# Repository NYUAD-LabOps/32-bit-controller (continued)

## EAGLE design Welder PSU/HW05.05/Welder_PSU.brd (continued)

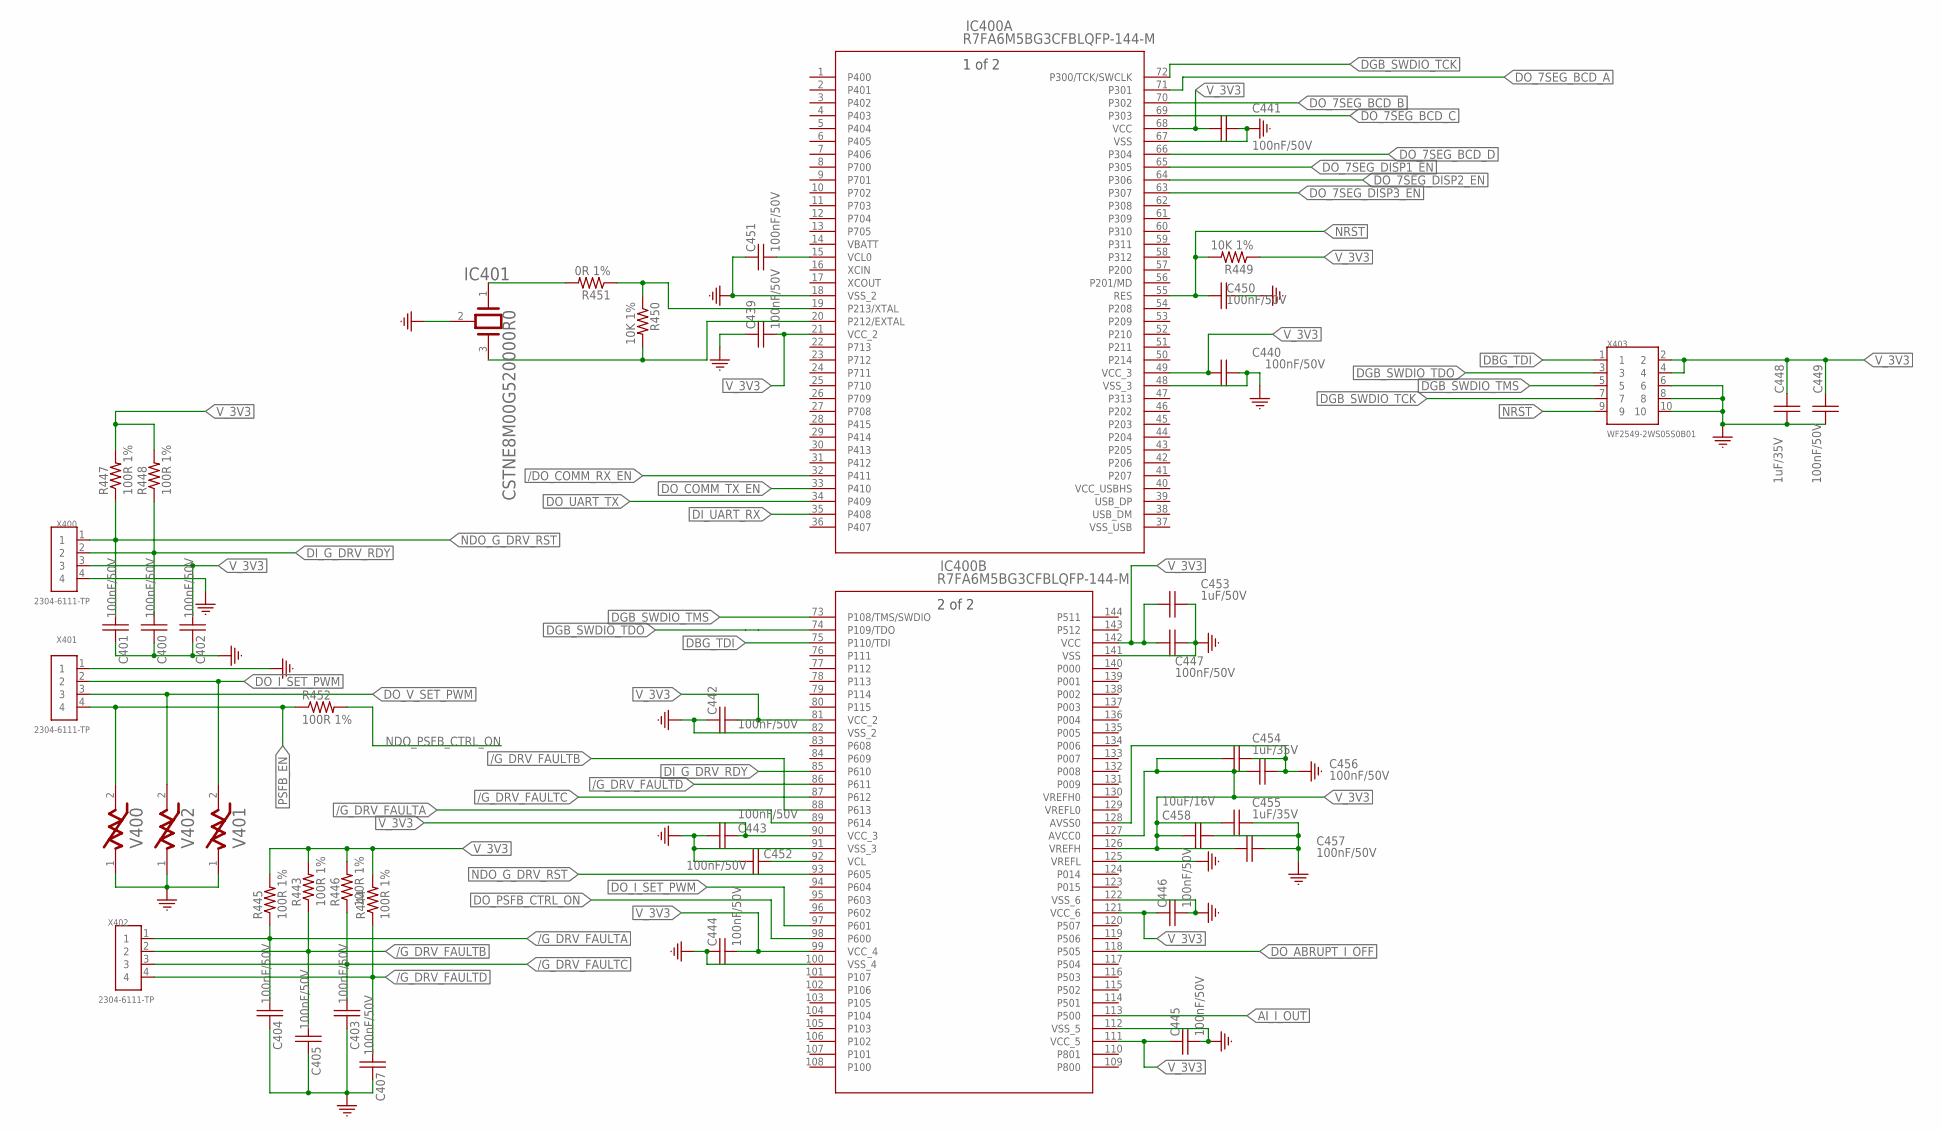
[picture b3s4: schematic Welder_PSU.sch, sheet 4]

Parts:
C400, C401, C402, C403, C404, C405, C407, C439, C440, C441, C442, C443, C444, C445, C446, C447, C449, C450, C451, C452, C456, C457: 100nF/50V; EIA0603
C448, C454, C455: 1uF/35V; EIA0603
C453: 1uF/50V; EIA0603
C458: 10uF/16V; EIA0603
IC400: R7FA6M5BG3CFBLQFP-144-M; LQFP-144-M
IC401: CSTNE8M00G520000R0
R443, R444, R445, R446, R447, R448, R452: 100R 1%; EIA0603
R449, R450: 10K 1%; EIA0603
R451: 0R 1%; EIA0603
V400, V401, V402: 0603ESDA-24NSMD; EIA0603
X400, X401, X402: 2304-6111-TP; X04_100MIL
X403: WF2549-2WS05S0B01; X10_100MIL_2XROW_VERT

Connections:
/DO_COMM_RX_EN: IC400.32 (P411); also elsewhere on the board
/G_DRV_FAULTA: C404.2, IC400.89 (P614), R445.1, X402.1; also elsewhere on the board
/G_DRV_FAULTB: C405.2, IC400.88 (P613), R443.1, X402.2; also elsewhere on the board
/G_DRV_FAULTC: C403.2, IC400.87 (P612), R446.1, X402.3; also elsewhere on the board
/G_DRV_FAULTD: C407.2, IC400.86 (P611), R444.1, X402.4; also elsewhere on the board
AI_I_OUT: IC400.113 (P500); also elsewhere on the board
DBG_TDI: IC400.75 (P110/TDI), X403.1
DGB_SWDIO_TCK: IC400.72 (P300/TCK/SWCLK), X403.7
DGB_SWDIO_TDO: IC400.74 (P109/TDO), X403.3
DGB_SWDIO_TMS: IC400.73 (P108/TMS/SWDIO), X403.5
DI_G_DRV_RDY: C400.2, IC400.85 (P610), R448.1, X400.2; also elsewhere on the board
DI_UART_RX: IC400.35 (P408); also elsewhere on the board
DO_7SEG_BCD_A: IC400.71 (P301); also elsewhere on the board
DO_7SEG_BCD_B: IC400.70 (P302); also elsewhere on the board
DO_7SEG_BCD_C: IC400.69 (P303); also elsewhere on the board
DO_7SEG_BCD_D: IC400.66 (P304); also elsewhere on the board
DO_7SEG_DISP1_EN: IC400.65 (P305); also elsewhere on the board
DO_7SEG_DISP2_EN: IC400.64 (P306); also elsewhere on the board
DO_7SEG_DISP3_EN: IC400.63 (P307); also elsewhere on the board
DO_ABRUPT_I_OFF: IC400.118 (P505); also elsewhere on the board
DO_COMM_TX_EN: IC400.33 (P410); also elsewhere on the board
DO_I_SET_PWM: IC400.97 (P601), V401.2, X401.2; also elsewhere on the board
DO_PSFB_CTRL_ON: IC400.98 (P600)
DO_UART_TX: IC400.34 (P409); also elsewhere on the board
DO_V_SET_PWM: V402.2, X401.3; also elsewhere on the board
GND: C400.1, C401.1, C402.1, C403.1, C404.1, C405.1, C407.1, C439.1, C440.2, C441.2, C442.1, C443.1, C444.1, C445.2, C446.2, C447.2, C448.1, C449.1, C450.2, C451.1, C452.2, C453.2, C454.2, C455.2, C456.2, C457.2, C458.2, IC400.18 (VSS_2), IC400.48 (VSS_3), IC400.67 (VSS), IC400.82 (VSS_2), IC400.91 (VSS_3), IC400.100 (VSS_4), IC400.112 (VSS_5), IC400.122 (VSS_6), IC400.125 (VREFL), IC400.128 (AVSS0), IC400.141 (VSS), IC401.2 (GND), V400.1, V401.1, V402.1, X400.4, X401.1, X403.6, X403.8, X403.10; also elsewhere on the board
unnamed: C451.2, IC400.15 (VCL0)
unnamed: C452.1, IC400.92 (VCL)
unnamed: IC400.20 (P212/EXTAL), IC401.3 (OUTPUT), R450.2
unnamed: IC401.1 (INPUT), R451.2
unnamed: IC400.19 (P213/XTAL), R450.1, R451.1
NDO_G_DRV_RST: C401.2, IC400.93 (P605), R447.1, X400.1; also elsewhere on the board
NDO_PSFB_CTRL_ON: R452.2
NRST: C450.1, IC400.55 (RES), R449.2, X403.9
PSFB_EN: R452.1, V400.2, X401.4; also elsewhere on the board
VBATT: IC400.14 (VBATT)
VCC_USBHS: IC400.40 (VCC_USBHS)
VREFH0: IC400.130 (VREFH0)
VREFL0: IC400.129 (VREFL0)
VSS_USB: IC400.37 (VSS_USB)
V_3V3: C402.2, C439.2, C440.1, C441.1, C442.2, C443.2, C444.2, C445.1, C446.1, C447.1, C448.2, C449.2, C453.1, C454.1, C455.1, C456.1, C457.1, C458.1, IC400.21 (VCC_2), IC400.49 (VCC_3), IC400.68 (VCC), IC400.81 (VCC_2), IC400.90 (VCC_3), IC400.99 (VCC_4), IC400.111 (VCC_5), IC400.121 (VCC_6), IC400.126 (VREFH), IC400.127 (AVCC0), IC400.142 (VCC), R443.2, R444.2, R445.2, R446.2, R447.2, R448.2, R449.1, X400.3, X403.2, X403.4; also elsewhere on the board

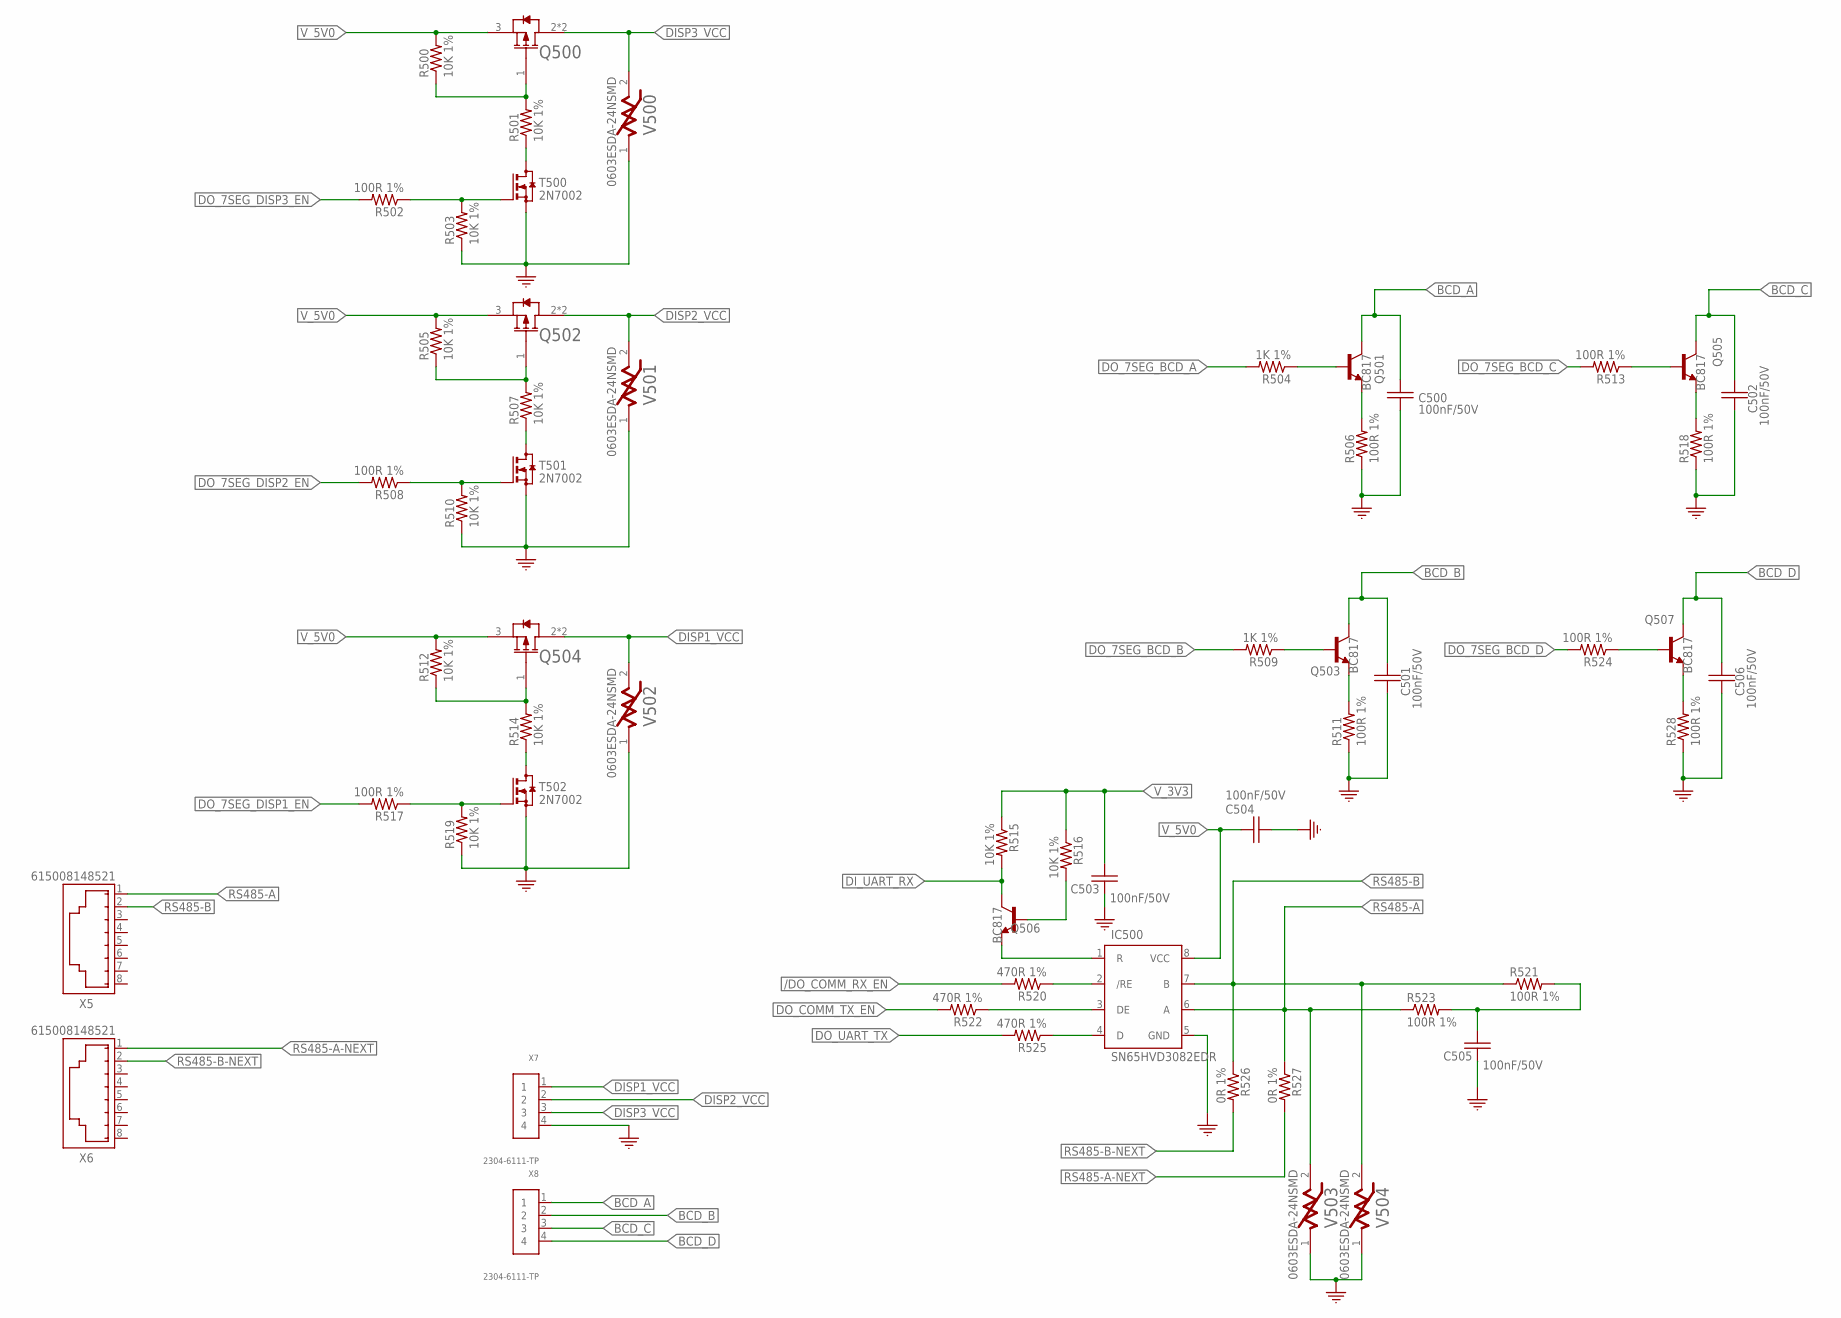
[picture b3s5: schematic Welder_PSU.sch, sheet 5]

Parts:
C500, C501, C502, C503, C504, C505, C506: 100nF/50V; EIA0603
IC500: SN65HVD3082EDR; SOIC8
Q500, Q502, Q504: DMP6185SEQ-13; SOT223
Q501, Q503, Q505, Q506, Q507: BC817; SOT23
R500, R501, R503, R505, R507, R510, R512, R514, R515, R516, R519: 10K 1%; EIA0603
R502, R506, R508, R511, R513, R517, R518, R521, R523, R524, R528: 100R 1%; EIA0603
R504, R509: 1K 1%; EIA0603
R520, R522, R525: 470R 1%; EIA0603
R526, R527: 0R 1%; EIA0603
T500, T501, T502: 2N7002; SOT23
V500, V501, V502, V503, V504: 0603ESDA-24NSMD; EIA0603
X5, X6: 615008148521
X7, X8: 2304-6111-TP; X04_100MIL

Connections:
/DO_COMM_RX_EN: R520.2; also elsewhere on the board
BCD_A: C500.1, Q501.3 (C), X8.1
BCD_B: C501.1, Q503.3 (C), X8.2
BCD_C: C502.1, Q505.3 (C), X8.3
BCD_D: C506.1, Q507.3 (C), X8.4
DISP1_VCC: Q504.2 (DRAIN), Q504.4 (DRAIN), V502.2, X7.1
DISP2_VCC: Q502.2 (DRAIN), Q502.4 (DRAIN), V501.2, X7.2
DISP3_VCC: Q500.2 (DRAIN), Q500.4 (DRAIN), V500.2, X7.3
DI_UART_RX: Q506.3 (C), R515.2; also elsewhere on the board
DO_7SEG_BCD_A: R504.2; also elsewhere on the board
DO_7SEG_BCD_B: R509.2; also elsewhere on the board
DO_7SEG_BCD_C: R513.2; also elsewhere on the board
DO_7SEG_BCD_D: R524.2; also elsewhere on the board
DO_7SEG_DISP1_EN: R517.2; also elsewhere on the board
DO_7SEG_DISP2_EN: R508.2; also elsewhere on the board
DO_7SEG_DISP3_EN: R502.2; also elsewhere on the board
DO_COMM_TX_EN: R522.2; also elsewhere on the board
DO_UART_TX: R525.2; also elsewhere on the board
GND: C500.2, C501.2, C502.2, C503.1, C504.1, C505.1, C506.2, IC500.5 (GND), R503.1, R506.1, R510.1, R511.1, R518.1, R519.1, R528.1, T500.2 (S), T501.2 (S), T502.2 (S), V500.1, V501.1, V502.1, V503.1, V504.1, X7.4; also elsewhere on the board
unnamed: C505.2, R521.2, R523.2
unnamed: IC500.1 (R), Q506.2 (E)
unnamed: Q506.1 (B), R516.2
unnamed: Q501.1 (B), R504.1
unnamed: IC500.2 (/RE), R520.1
unnamed: Q501.2 (E), R506.2
unnamed: IC500.3 (DE), R522.1
unnamed: IC500.4 (D), R525.1
unnamed: Q503.1 (B), R509.1
unnamed: Q503.2 (E), R511.2
unnamed: Q505.1 (B), R513.1
unnamed: Q505.2 (E), R518.2
unnamed: Q507.1 (B), R524.1
unnamed: Q507.2 (E), R528.2
unnamed: R508.1, R510.2, T501.1 (G)
unnamed: R502.1, R503.2, T500.1 (G)
unnamed: R501.1, T500.3 (D)
unnamed: Q500.1 (GATE), R500.1, R501.2
unnamed: R507.1, T501.3 (D)
unnamed: Q502.1 (GATE), R505.1, R507.2
unnamed: R517.1, R519.2, T502.1 (G)
unnamed: R514.1, T502.3 (D)
unnamed: Q504.1 (GATE), R512.1, R514.2
RS485-A: IC500.6 (A), R523.1, R527.1, V503.2, X5.1
RS485-A-NEXT: R527.2, X6.1
RS485-B: IC500.7 (B), R521.1, R526.1, V504.2, X5.2
RS485-B-NEXT: R526.2, X6.2
V_3V3: C503.2, R515.1, R516.1; also elsewhere on the board
V_5V0: C504.2, IC500.8 (VCC), Q500.3 (SOURCE), Q502.3 (SOURCE), Q504.3 (SOURCE), R500.2, R505.2, R512.2; also elsewhere on the board

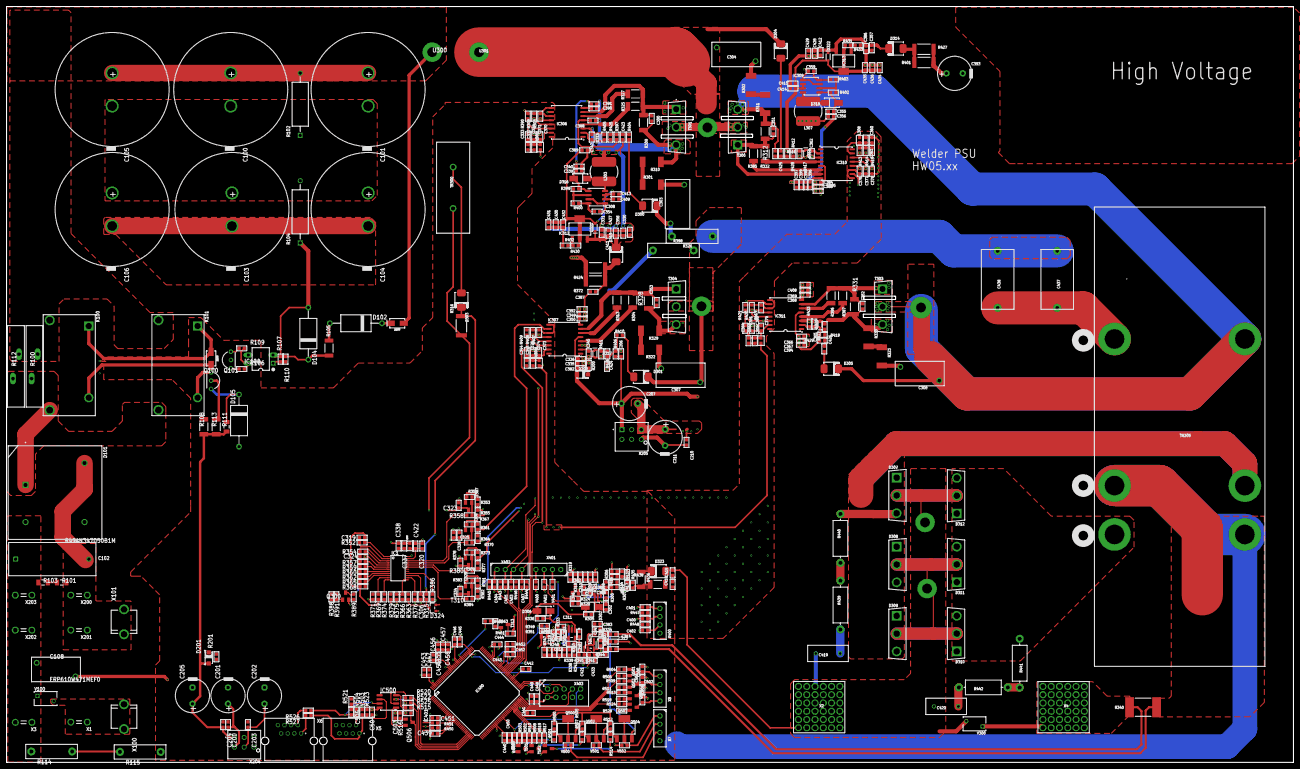
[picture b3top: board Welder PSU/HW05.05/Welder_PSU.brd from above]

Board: 4 copper layers, 395.0 x 232.0 mm, 494 parts (0 on the bottom side), 223 nets.

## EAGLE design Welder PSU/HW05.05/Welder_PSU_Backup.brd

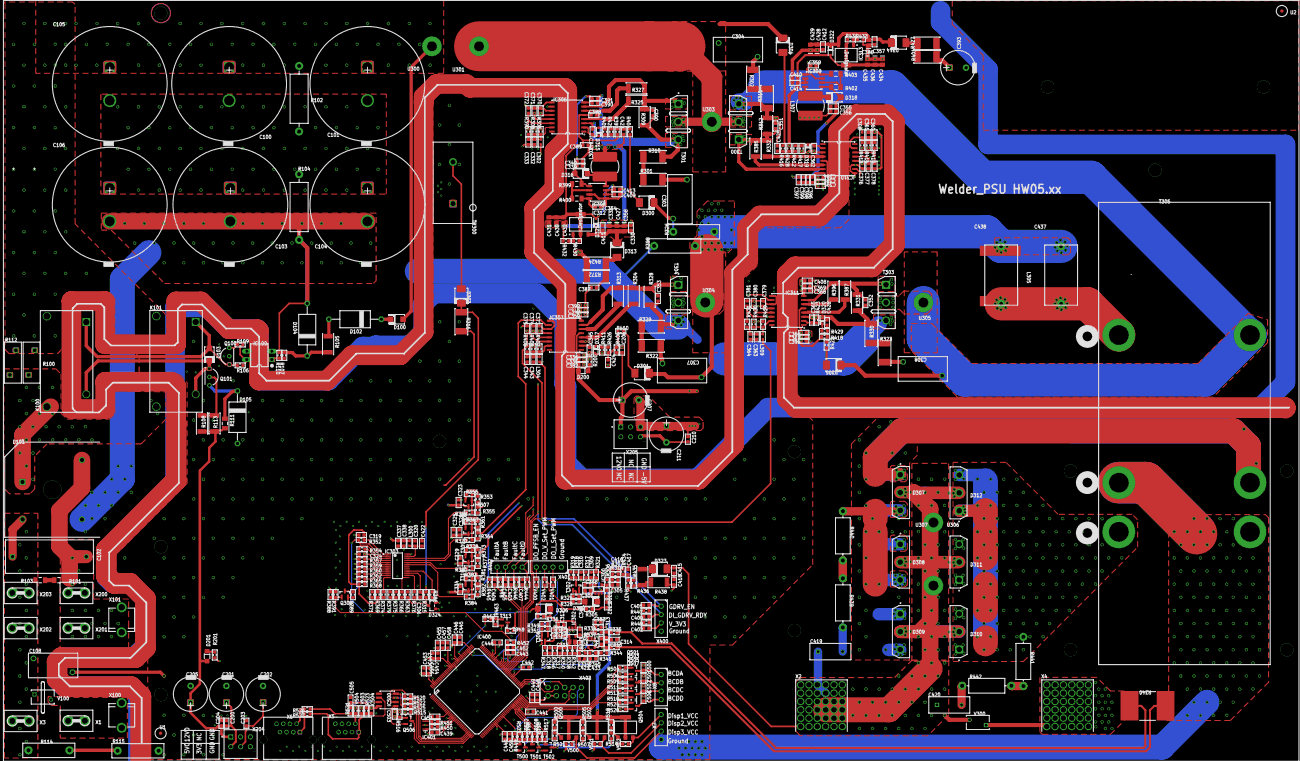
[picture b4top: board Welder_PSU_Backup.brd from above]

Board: 2 copper layers, 515 parts (0 on the bottom side), 159 nets.

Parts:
C100, C101, C103: 1500µF/250V; CAPACITOR-ELKO-400V-RM10-35X76PRIMARY
C102: 470nF/275AC; CP22.5X10X26.5_1PRIMARY
C104: 1500µF/250V; CAPACITOR-ELKO-400V-RM10-35X77PRIMARY
C105, C106: 1500µF/250V; CAPACITOR-ELKO-400V-RM10-35X74PRIMARY
C108: 470pF/760V; CAPACITOR-FILM-RM12.5MM-12MM_1PRIMARY
C200, C203, C204, C206, C210, C305, C309, C310, C317, C318, C323, C324, C328, C329, C330, C332, C334, C335, C338, C340, C343, C346, C347, C348, C349, C354, C357, C359, C361, C363, C366, C368, C385, C400, C401, C402, C403, C404, C405, C407, C411, C412, C413, C414, C422, C439, C440, C441, C442, C443, C444, C445, C446, C447, C449, C450, C451, C452, C456, C457: 100nF/50V; EIA0603_3PRIMARY
C201: 470µF; CAPACITOR-ELKO-RM5-10X20_6PRIMARY
C202: 470µF; CAPACITOR-ELKO-RM5-10X20_5PRIMARY
C205: 470µF; CAPACITOR-ELKO-RM5-10X20_4PRIMARY
C207: 470µF; CAPACITOR-ELKO-RM5-10X20_3PRIMARY
C211: 470µF; CAPACITOR-ELKO-RM5-10X20_2PRIMARY
C300, C301, C351: 470pF/50V; EIA0603_3PRIMARY
C302: 22nF/50V; EIA0603_3PRIMARY
C303, C304, C307, C308: 470pF/15KV; CAPACITOR-FILM-RM12.5MM-12MM_1PRIMARY
C306, C352, C353, C423, C424, C425, C426: 330pF/50V; EIA0603_3PRIMARY
C311: 12pF/50V; EIA0603_3PRIMARY
C312: 510pF/50V; EIA0603_3PRIMARY
C313, C316: 10nF/50V; EIA0603_3PRIMARY
C314, C342, C345, C362, C365: 1nF/50V; EIA0603_3PRIMARY
C315: 22uF/16V; EIA0805_1PRIMARY
C319, C320: 1uF/25V; EIA0603_3PRIMARY
C325, C333, C337, C344, C360, C364: 1uF/50V; EIA0603_3PRIMARY
C331, C358, C386, C427, C428, C429, C430, C431, C432, C434, C435, C436: 10uF/50V; EIA0805_1PRIMARY
C336: 10uF/50V; EIA0603_3PRIMARY
C339, C355, C367, C382, C392, C394, C398, C399, C408: 10uF/35V; EIA0603_3PRIMARY
C350: 2.2uF/50V; EIA0603_3PRIMARY
C356: 4.7uF/25V; EIA0603_3PRIMARY
C369: 2.2uF/35V; EIA0603_3PRIMARY
C370, C371, C372, C373, C374, C375, C376, C377, C378, C379, C380, C381: 100pF/50V; EIA0603_3PRIMARY
C383, C433: 100pF/25V; EIA0603_3PRIMARY
C384, C409, C410: 4.7uF/50V; EIA0603_3PRIMARY
C387, C415, C418, C500, C501, C502, C505, C506: 100nF/100V; EIA0603_3PRIMARY
C388, C389, C390, C391, C395, C396, C397, C416, C417: 10uF/25V; EIA0603_3PRIMARY
C393: 470µF; CAPACITOR-ELKO-RM5-10X20_1PRIMARY
C419, C420: 1nF/3KV; C_DISC_P7.5D12_1PRIMARY
C421: 220nF/25V; EIA0603_3PRIMARY
C437, C438: 2.4uF/400V; CAPACITOR-FILM-RM17.5-28X17.55PRIMARY
C448, C453, C454, C455: 1uF/16V; EIA0603_3PRIMARY
C458: 10uF/16V; EIA0603_3PRIMARY
C503, C504: 100nF/25V; EIA0603_3PRIMARY
D100, D103: RS1M-13-F; SMA_2PRIMARY
D101: GBPC3510W; GBPC3510W_1PRIMARY
D102: 1N5387BRLG; DO-201AD_1PRIMARY
D104, D105: 9.1V; DO-201AD_1PRIMARY
D200, D201: 26-21/GPC-F3138B/CA; 1206LED_1PRIMARY
D300, D301, D303, D304, D305, D323: STTH1R04U; SMB_1PRIMARY
D302, D306, D316, D318: SS14; SMA_1PRIMARY
D307, D308, D309, D310, D311, D312: 15A,_600V; TO247-AD_1PRIMARY
D313, D314: GB02SLT12-214; SMB_1PRIMARY
D315, D317, D319, D320, D321, D322: SD103AW; SOD323_1PRIMARY
D324: BAT54S; SOT23DUALDIODE_1PRIMARY
DUMMY1, DUMMY2, DUMMY3, DUMMY4, DUMMY5, DUMMY6, DUMMY7, DUMMY8, DUMMY9, DUMMY10, DUMMY11, DUMMY12, DUMMY13: P:EX157Y157D1571
IC100: PC817; DIP04_1PRIMARY
IC300, IC301, IC302: LMV641; SOT23-5_1PRIMARY
IC303: UCC28951; TSSOP24_1PRIMARY
IC306, IC307, IC310, IC311: UCC21710; SOIC16_WIDE_HV_1PRIMARY
IC308, IC309: MAX764; SOIC8_1PRIMARY
IC312, IC313: LM317; SOT223_TI_1PRIMARY
IC400: R7FA6M5; QFP-144-M_1PRIMARY
IC401: 8MHz; RESONATOR_CSTNE8M00G520000R0_1PRIMARY
IC500: RS-485_TxRx; SOIC8_1PRIMARY
K100, K101: ALFG2PF09; ALFG2PF09_1PRIMARY
L300, L302, L304, L308, L309: 600R@100MHz; FERRITE_SMD_0603_1PRIMARY
L303, L307: 47µH; SRN8040TA_1PRIMARY
L305: 1uH; SRP1770TA_1PRIMARY
Q100: BC640TA; TO-92_1PRIMARY
Q101: KSD1616AYTA; TO-92_1PRIMARY
Q300: 2N7002; SOT23-3N_1PRIMARY
Q500, Q502, Q504: DMP6185SEQ-13; SOT223_1PRIMARY
Q501, Q503, Q505, Q507: BC817-25; SOT23-3N_2PRIMARY
Q506: BC817-40; SOT23-3N_2PRIMARY
R100, R112: 120R,3.5A; NTC_D10_P7.5_1PRIMARY
R101, R103: 220K_5%; EIA1206_1PRIMARY
R102, R104: 100K_5%; RES-RM20-RSF2W_1PRIMARY
R105: 82K_1%; 2010RESISTOR_1PRIMARY
R106, R354, R379, R451, R526, R527: 0R_1%; EIA0603_2PRIMARY
R107, R109, R353, R361, R373, R381: 330R_1%; EIA0603_2PRIMARY
R108, R113: 18R_1%; 2010RESISTOR_1PRIMARY
R110, R342: 220K_1%; EIA0603_2PRIMARY
R111: 1K_1%; EIA1206_1PRIMARY
R114, R115, R326, R398: 10_Meg; RES-RM12.5-VR37_1PRIMARY
R200, R315, R418, R504, R509, R513, R524: 1K_1%; EIA0603_2PRIMARY
R201: 1k_1%; EIA0603_2PRIMARY
R300, R334, R345, R360, R365, R368, R437: 100K_1%; EIA0603_2PRIMARY
R301, R302, R310, R311, R322, R323, R329, R330: 47R; 2512RESISTOR_1PRIMARY
R303, R308, R390, R407, R408, R409, R413, R414, R415, R419, R420, R421: 4.7K_1%; EIA0603_2PRIMARY
R304, R313, R325, R332, R387, R396: 33R_1%; 2010RESISTOR_1PRIMARY
R305, R306, R307, R314, R317, R318, R319, R320, R321, R324, R336, R343, R349, R350, R351, R355, R356, R363, R364, R366, R367, R377, R378, R382, R383, R429, R443, R444, R445, R446, R447, R448, R449, R450, R500, R501, R503, R505, R507, R510, R512, R514, R519: 10K_1%; EIA0603_2PRIMARY
R309, R312, R328, R331: 1K_1%; 2010RESISTOR_1PRIMARY
R316: 12R_1%; 2512RESISTOR_1PRIMARY
R327, R385: 22R_1%; 2010RESISTOR_1PRIMARY
R333, R369, R371: 150K_1%; EIA0603_2PRIMARY
R335, R344: 1.5k_1%; EIA0603_2PRIMARY
R337, R341: 510R_1%; EIA0603_2PRIMARY
R338: 33K_1%; EIA0603_2PRIMARY
R339: 162R_1%; EIA0603_2PRIMARY
R340: 300uR_1%; WSLP3921L_1PRIMARY
R346, R347, R348: 3.3K_1%; EIA0603_2PRIMARY
R352, R374: 18K_1%; EIA0603_2PRIMARY
R357, R359: 49.9K_1%; EIA0603_2PRIMARY
R358, R370, R380, R384, R461, R462: 10R_1%; EIA0603_2PRIMARY
R362: 65K_1%; EIA0603_2PRIMARY
R372, R401, R424, R427: 10R; 2512RESISTOR_1PRIMARY
R375, R376: 470R_1%; EIA0603_2PRIMARY
R386, R388: 10K_1%; EIA0603_1PRIMARY
R389: 825K_1%; EIA0603_1PRIMARY
R391: 3.3K_1%; EIA0603_1PRIMARY
R397, R406, R412, R425, R426, R428: 5.6K_1%; EIA0603_2PRIMARY
R399, R402: 33k_1%; EIA1206_1PRIMARY
R400, R403: 10k_1%; EIA1206_1PRIMARY
R404, R410, R416, R422: 220R_1%; EIA0603_2PRIMARY
R405, R411, R417, R423: 2.2K_1%; EIA0603_2PRIMARY
R430, R431: 1K; EIA0603_2PRIMARY
R432, R433: 8.66K; EIA0603_2PRIMARY
R434, R435: 15.8K_1%; EIA0603_2PRIMARY
R436: 41K_1%; 2010RESISTOR_1PRIMARY
R438: 1.2K_1%; 2010RESISTOR_1PRIMARY
R439, R440, R441, R442: 22R,_5%_2W; RES-RM15-RSF1W_1PRIMARY
R452, R502, R506, R508, R511, R517, R518, R521, R523, R528: 100R_1%; EIA0603_2PRIMARY
R463: 10k_1%; EIA0603_2PRIMARY
R515, R516: 10k; EIA0603_2PRIMARY
R520, R522, R525: 470R; EIA0603_2PRIMARY
T300, T301, T303: STGW30H60DFB; TO247-AC_2PRIMARY
T302, T306, T307, T308, T309, T310, T313: 2N7002; SOT23-3N_2PRIMARY
T304: STGW30H60DFB; TO247-AC_1PRIMARY
T305: PSFB_Tr.; 11-0060-A_1PRIMARY
T500, T501, T502: Value; SOT23-3N_2PRIMARY
TR300: 56mH; CST206-2A_1PRIMARY
U1, U2: FiducialMarker; FIDUCIALMARKER_1PRIMARY
U300: WireHole; PAD-3.0X6.0MM_7PRIMARY
U301: WireHole; PAD-3.0X6.0MM_6PRIMARY
U303: WireHole; PAD-3.0X6.0MM_5PRIMARY
U304: Value; PAD-3.0X6.0MM_4PRIMARY
U305: Value; PAD-3.0X6.0MM_3PRIMARY
U306: WireHole; PAD-3.0X6.0MM_2PRIMARY
U307: WireHole; PAD-3.0X6.0MM_1PRIMARY
V100, V300: 430V/8.6J; EPCOS_B72205S0271K101_1PRIMARY
V400, V401, V402: CG0603MLC-05E; EIA0603_2PRIMARY
V500, V501, V502, V503, V504: 0603ESDA-24N; EIA0603_2PRIMARY
X1, X3: 6.3_X_0.8mm; X01_FASTONPCBTAB6.3MM1.8MMHO87PRIMARY
X2, X4: M10_Screw_Terminal; X01_M10_7461061_1PRIMARY
X5, X6: RJ45; X08_615008148521_1PRIMARY
X7, X8, X400, X401, X402: X04_100mil; X04_100MIL_1PRIMARY
X100, X101: Fuse_Clip; FUSE_CLIP_01020071Z_1PRIMARY
X200, X201, X202, X203: Value; X01_FASTONPCBTAB6.3MM1.8MMHO87PRIMARY
X204, X205: X06_Molex_Microfit; X06_MOLEX_MICROFIT_1PRIMARY
X403: Package; X10_100MIL_2XROW_VERT_1PRIMARY

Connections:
AI_I_OUT: C433.2, IC301.1, IC400.113, R339.2, R345.2
COMM_TX_EN: IC400.33, R522.1
CTRLR_OUTA: IC303.22, R358.1
CTRLR_OUTB: IC303.21, R370.1
CTRLR_OUTC: IC303.20, R380.1
CTRLR_OUTD: IC303.19, R384.1
DI_UART_RX: IC400.35, Q506.3, R515.1
DO_7SEG_BCD_A: IC400.71, R504.2
DO_7SEG_BCD_B: IC400.70, R509.2
DO_7SEG_BCD_C: IC400.69, R513.2
DO_7SEG_BCD_D: IC400.66, R524.2
DO_7SEG_DISP1_EN: IC400.65, R517.2
DO_7SEG_DISP2_EN: IC400.64, R508.2
DO_7SEG_DISP3_EN: IC400.63, R502.2
DO_ABRUPT_I_OFF: IC400.118, R462.2
DO_UART_TX: IC400.34, R525.1
EA_IN: D302.1, D306.1, IC303.2, R305.2, R336.2, R352.2, R461.1
G_DRV1_VCC: C332.2, C333.2, R303.1, R308.1, R390.1
G_DRV2_VCC: C343.2, C344.2, R407.1, R408.1, R409.1
G_DRV3_VCC: C360.2, C361.2, R413.1, R414.1, R415.1
G_DRV4_VCC: C363.2, C364.2, R419.1, R420.1, R421.1
G_DRV_INA: R353.1, R355.1
G_DRV_INB: R361.1, R364.1
G_DRV_INC: R373.1, R377.1
G_DRV_IND: R381.1, R382.1
NETC301_1: C301.1, C305.2, IC300.4, R300.1, R306.2
NETC301_2: C301.2, C302.2, D302.2, IC300.1, R305.1
NETC302_1: C302.1, R300.2
NETC305_1: C305.1, R314.2
NETC309_2: C309.2, IC300.3, R317.2, R321.1
NETC310_2: C310.2, R317.1, R318.2
NETC311_1: C311.1, C315.1, IC302.4, R333.1, R338.2
NETC311_2: C311.2, C312.2, D306.2, IC302.1, R336.1
NETC312_1: C312.1, R333.2
NETC313_1: C313.1, C314.2, C316.2
NETC313_2: C313.2, R335.1, R337.2
NETC315_2: C315.2, R342.2
NETC316_1: C316.1, R341.2, R344.1
NETC317_2: C317.2, IC302.3, R346.2, R350.1
NETC318_2: C318.2, R346.1, R347.2
NETC320_2: C320.2, C422.2
NETC354_2: C354.2, IC308.4, R400.1
NETC359_2: C359.2, IC309.4, R403.1
NETC383_1: C383.1, IC301.3, R334.2, R337.1
NETC415_1: C415.1, C418.2
NETC416_2: C416.2, R307.2, R434.1
NETC417_2: C417.2, R434.2, R435.1, R437.2
NETC421_2: C421.2, R338.1, R339.1, R342.1, R343.2
NETC423_1: C423.1, R397.1, R404.1, R425.2
NETC424_2: C424.2, R406.1, R410.1, R426.2
NETC425_2: C425.2, R412.2, R416.1, R428.1
NETC426_2: C426.2, R418.1, R422.1, R429.2
NETC433_1: C433.1, IC301.4, R341.1, R345.1
NETC451_1: C451.1, IC400.15
NETC452_1: C452.1, IC400.92
NETC505_2: C505.2, R521.2, R523.2
NETD100_K: D100.2, D102.2
NETD101_1: D101.1, K100.4, K101.4, R100.2, R112.2
NETD103_A: D103.1, K100.1, K101.1, Q100.1, R106.2
NETD103_K: D103.2, K100.2, K101.2, Q101.1
NETD104_K: D104.2, R107.2
NETD105_K: D105.2, Q101.3, R111.1
NETD200_1: D200.1, R200.2
NETD201_1: D201.1, R201.2
NETD300_A: D300.1, R404.2
NETD301_A: D301.1, R410.2
NETD303_A: D303.1, TR300.2
NETD304_A: D304.1, R416.2
NETD305_A: D305.1, R422.2
NETD307_1: D307.1, D307.3, D308.1, D308.3, D309.1, D309.3, R440.1, T305.5
NETD310_1: D310.1, D310.3, D311.1, D311.3, D312.1, D312.3, R441.1, T305.3
NETD316_2: D316.2, IC308.8, L303.2
NETD318_2: D318.2, IC309.8, L307.2
NETIC100_1: IC100.1, R107.1, R110.2
NETIC100_4: IC100.4, R106.1, R109.1
NETIC303_3: IC303.3, R354.1
NETIC303_4: IC303.4, R354.2
NETIC303_6: IC303.6, R357.2
NETIC303_7: IC303.7, R359.2
NETIC303_8: IC303.8, R360.2
NETIC303_9: IC303.9, R362.2
NETIC303_10: IC303.10, R365.1, R368.1
NETIC303_11: IC303.11, R369.2, R371.2
NETIC303_12: IC303.12, R374.1, R379.1
NETIC303_13: IC303.13, R366.2, R375.2
NETIC303_14: IC303.14, R363.2, R376.2
NETIC303_16: IC303.16, R386.2
NETIC308_2: IC308.2, R399.2, R400.2
NETIC309_2: IC309.2, R402.2, R403.2
NETIC312_1: IC312.1, R430.1, R432.2
NETIC313_1: IC313.1, R431.1, R433.2
NETIC400_19: IC400.19, R450.1, R451.1
NETIC400_20: IC400.20, R450.2
NETIC500_1: IC500.1, Q506.2
NETIC500_2: IC500.2, R520.2
NETIC500_3: IC500.3, R522.2
NETIC500_4: IC500.4, R525.2
NETQ100_3: Q100.3, R109.2
NETQ500_1: Q500.1, R500.1, R501.2
NETQ501_1: Q501.1, R504.1
NETQ501_2: Q501.2, R506.2
NETQ502_1: Q502.1, R505.1, R507.2
NETQ503_1: Q503.1, R509.1
NETQ503_2: Q503.2, R511.2
NETQ504_1: Q504.1, R512.1, R514.2
NETQ505_1: Q505.1, R513.1
NETQ505_2: Q505.2, R518.2
NETQ506_1: Q506.1, R516.1
NETQ507_1: Q507.1, R524.1
NETQ507_2: Q507.2, R528.2
NETR101_1: R101.1, R103.2
NETR114_1: R114.1, R115.2
NETR306_1: R306.1, R307.1, R314.1
NETR318_1: R318.1, R319.1, T302.3
NETR320_1: R320.1, R324.2, T302.1
NETR347_1: R347.1, R348.1, T306.3
NETR349_1: R349.1, R351.2, T306.1
NETR353_2: R353.2, R356.2, T307.2
NETR356_1: R356.1, R358.2, T307.1
NETR361_2: R361.2, R367.2, T308.2
NETR367_1: R367.1, R370.2, T308.1
NETR373_2: R373.2, R378.2, T309.2
NETR378_1: R378.1, R380.2, T309.1
NETR381_2: R381.2, R383.2, T310.2
NETR383_1: R383.1, R384.2, T310.1
NETR439_1: R439.1, R440.2
NETR441_2: R441.2, R442.1
NETR461_2: R461.2, T313.3
NETR462_1: R462.1, R463.1, T313.1
NETR501_1: R501.1, T500.3
NETR502_1: R502.1, R503.2, T500.1
NETR507_1: R507.1, T501.3
NETR508_1: R508.1, R510.2, T501.1
NETR514_1: R514.1, T502.3
NETR517_1: R517.1, R519.2, T502.1
QA_GATE: C300.2, T301.1
QA_OC: C342.2, D315.2, R405.1, R425.1
QB_GATE: C353.2, T304.1
QB_OC: C345.2, D317.2, R411.1, R426.1
QC_GATE: C351.1, T300.1
QC_OC: C362.2, D319.2, R412.1, R417.1
QD_GATE: C352.1, T303.1
QD_OC: C365.2, D320.2, R423.1, R429.1
RS485-A: IC500.6, R523.1, R527.2, V503.2, X5.1
RS485-A-NEXT: R527.1, X6.1
RS485-B: IC500.7, R521.1, R526.2, V504.2, X5.2
RS485-B-NEXT: R526.1, X6.2
SS-EN: C324.1, IC303.5, Q300.3, R389.2
VDDA_REG: C388.1, C389.1, C409.2, C413.2, C430.2, C431.2, C432.2, D321.1, IC308.6, IC308.7, IC312.2, IC312.3, R397.2, R430.2
VDDC_REG: C384.1, C385.2, C395.1, C410.2, C414.2, C434.2, C435.2, C436.2, D322.1, IC309.6, IC309.7, IC313.2, IC313.3, R428.2, R431.2
VDD_A: C330.2, C331.2, C358.2, C411.2, C427.2, D313.2, D321.2, IC312.4
VDD_C: C357.2, C386.2, C412.2, C428.2, C429.2, D314.2, D322.2, IC313.4
VEE_A: C339.2, C340.2, C390.1, C391.1, D316.1, IC308.1, R399.1
VEE_C: C355.2, C356.2, C396.1, C397.1, C398.2, C399.2, D318.1, IC309.1, R402.1
VREF: C319.1, IC303.1, R352.1, R368.2, R369.1, R374.2
V_CS_F: C306.2, R315.1, R363.1, R366.1
V_RECT_F_PLUS: K101.3, R112.1
WELDER-: R335.2, R340.2, V300.1, X4.1, X4.2, X4.3, X4.4, X4.5, X4.6, X4.7, X4.8, X4.9, X4.10, X4.11, X4.12, X4.13, X4.14, X4.15, X4.16, X4.17, X4.18, X4.19, X4.20, X4.21, X4.22, X4.23, X4.24, X4.25, X4.26, X4.27, X4.28, X4.29, X4.30, X4.31, X4.32, X4.33, X4.34, X4.35, X4.36
_COMM_RX_EN: IC400.32, R520.1

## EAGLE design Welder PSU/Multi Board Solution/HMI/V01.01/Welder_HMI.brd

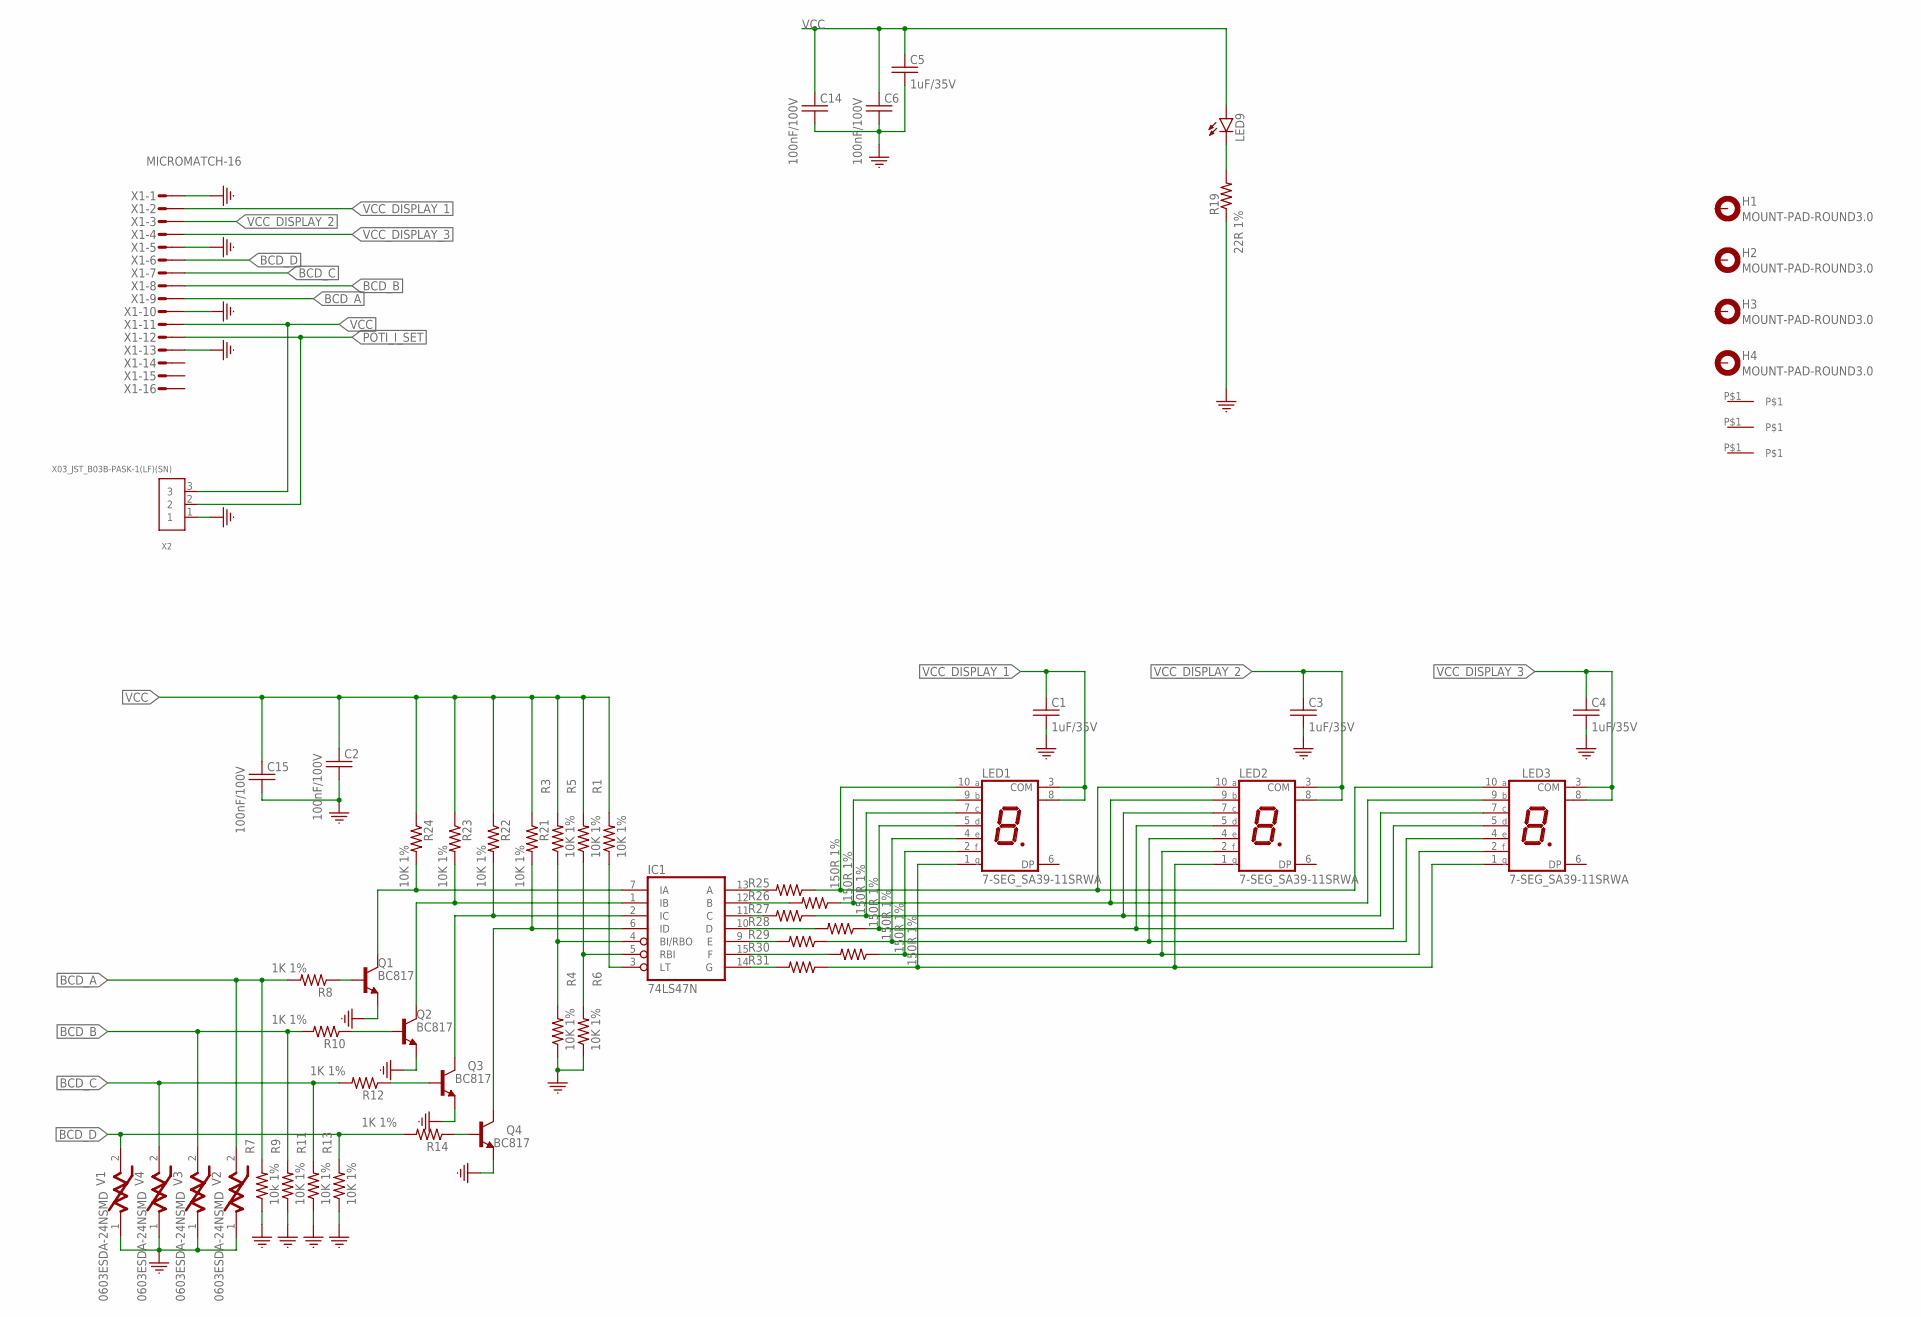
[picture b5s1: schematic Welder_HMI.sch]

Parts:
C1, C3, C4, C5: 1uF/35V; EIA0603
C2, C6, C14, C15: 100nF/100V; EIA0603
FID1, FID2, FID3: FIDUCIAL
H1, H2, H3, H4: MOUNT-PAD-ROUND3.0; 3,0-PAD
IC1: 74LS47N; DIL16
LED1, LED2, LED3: 7-SEG_SA39-11SRWA; SA39-11SRWA
LED9: LED5MM
Q1, Q2, Q3, Q4: BC817; SOT23
R1, R3, R4, R5, R6, R9, R11, R13, R21, R22, R23, R24: 10K 1%; EIA0603
R7: 10k 1%; EIA0603
R8, R10, R12, R14: 1K 1%; EIA0603
R19: 22R 1%; EIA1206
R25, R26, R27, R28, R29, R30, R31: 150R 1%; EIA1206
V1, V2, V3, V4: 0603ESDA-24NSMD; EIA0603
X1: MICROMATCH-16
X2: X03_JST_B03B-PASK-1(LF)(SN)

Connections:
BCD_A: R7.2, R8.2, V2.2, X1.9
BCD_B: R9.2, R10.2, V3.2, X1.8
BCD_C: R11.2, R12.2, V4.2, X1.7
BCD_D: R13.2, R14.2, V1.2, X1.6
GND: C1.2, C2.2, C3.2, C4.2, C5.2, C6.2, C14.2, C15.2, IC1.8 (GND), Q1.2 (E), Q2.2 (E), Q3.2 (E), Q4.2 (E), R4.1, R6.1, R7.1, R9.1, R11.1, R13.1, R19.1, V1.1, V2.1, V3.1, V4.1, X1.1, X1.5, X1.10, X1.13, X2.1
unnamed: LED1.10 (A), LED2.10 (A), LED3.10 (A), R25.1
unnamed: LED1.9 (B), LED2.9 (B), LED3.9 (B), R26.1
unnamed: LED1.7 (C), LED2.7 (C), LED3.7 (C), R27.1
unnamed: LED1.5 (D), LED2.5 (D), LED3.5 (D), R28.1
unnamed: LED1.4 (E), LED2.4 (E), LED3.4 (E), R29.1
unnamed: LED1.2 (F), LED2.2 (F), LED3.2 (F), R30.1
unnamed: LED1.1 (G), LED2.1 (G), LED3.1 (G), R31.1
unnamed: IC1.4 (BI/RBO), R3.1, R4.2
unnamed: IC1.3 (LT), R1.1
unnamed: Q4.1 (B), R14.1
unnamed: IC1.5 (RBI), R5.1, R6.2
unnamed: IC1.13 (A), R25.2
unnamed: Q3.1 (B), R12.1
unnamed: Q2.1 (B), R10.1
unnamed: Q1.1 (B), R8.1
unnamed: IC1.7 (IA), Q1.3 (C), R24.2
unnamed: IC1.1 (IB), Q2.3 (C), R23.2
unnamed: IC1.2 (IC), Q3.3 (C), R22.2
unnamed: IC1.6 (ID), Q4.3 (C), R21.2
unnamed: LED9.K (C), R19.2
unnamed: IC1.12 (B), R26.2
unnamed: IC1.11 (C), R27.2
unnamed: IC1.10 (D), R28.2
unnamed: IC1.9 (E), R29.2
unnamed: IC1.15 (F), R30.2
unnamed: IC1.14 (G), R31.2
POTI_I_SET: X1.12, X2.2
VCC: C2.1, C5.1, C6.1, C14.1, C15.1, IC1.16 (VCC), LED9.A, R1.2, R3.2, R5.2, R21.1, R22.1, R23.1, R24.1, X1.11, X2.3
VCC_DISPLAY_1: C1.1, LED1.3 (COM), LED1.8 (COM), X1.2
VCC_DISPLAY_2: C3.1, LED2.3 (COM), LED2.8 (COM), X1.3
VCC_DISPLAY_3: C4.1, LED3.3 (COM), LED3.8 (COM), X1.4
